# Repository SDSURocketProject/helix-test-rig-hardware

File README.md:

# Helix-Test-Rig-Hardware

Schematics for Helix Project test rig.

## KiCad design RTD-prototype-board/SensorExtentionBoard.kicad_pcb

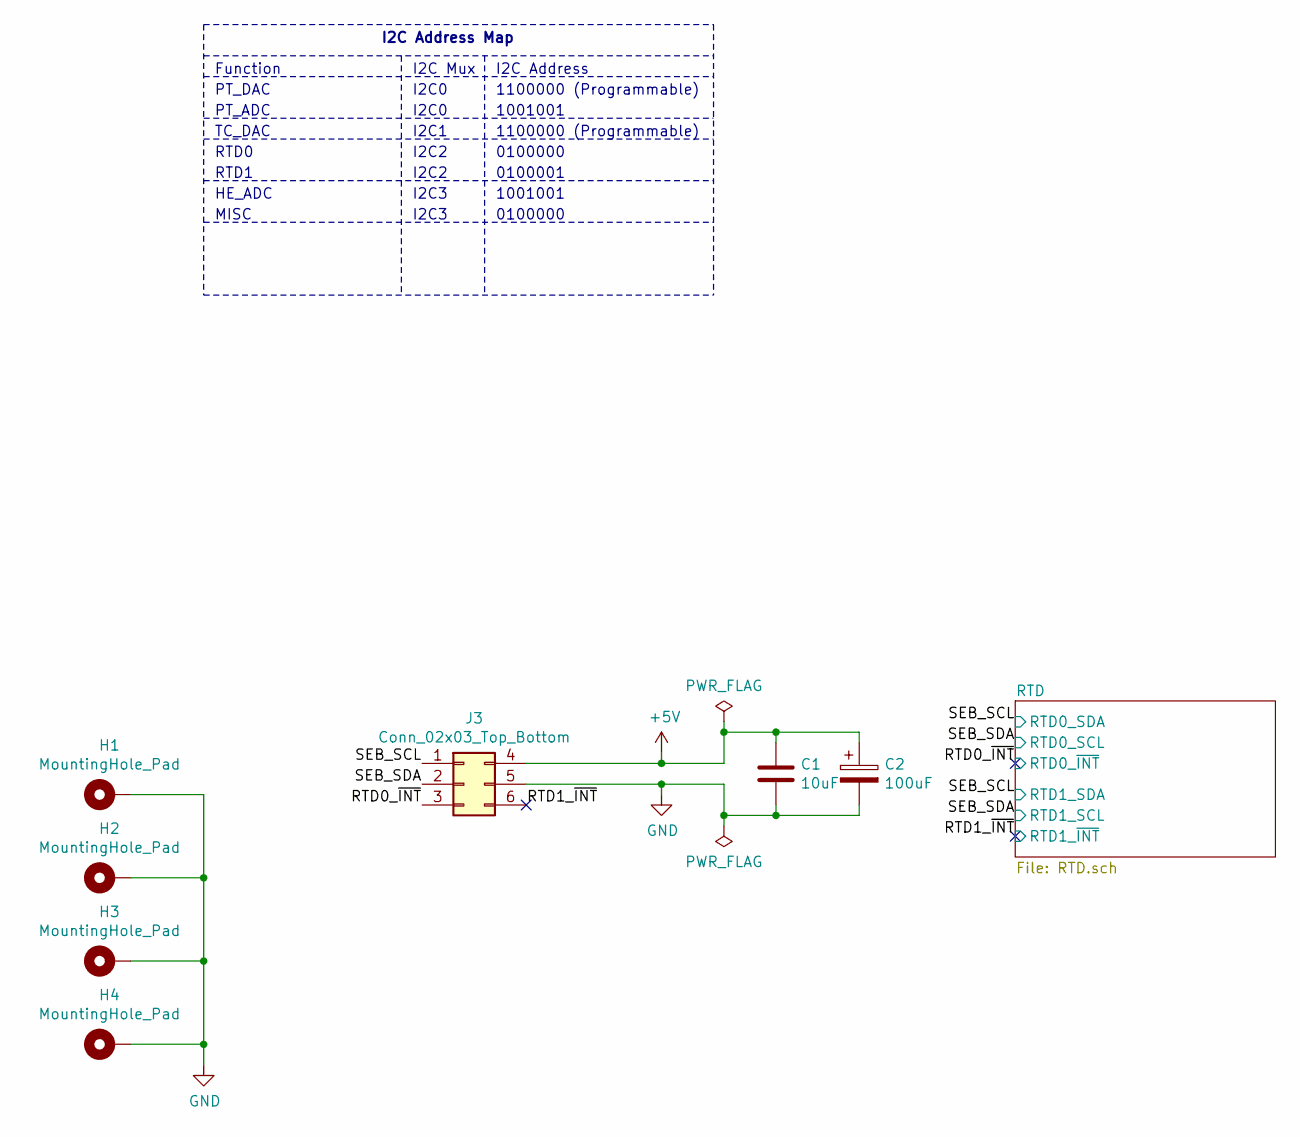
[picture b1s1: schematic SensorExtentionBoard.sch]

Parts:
C1: 10uF; C_1206_3216Metric_Pad1.42x1.75mm_HandSolder
C2: 100uF; CP_Elec_5x5.3
H1, H2, H3, H4: MountingHole_Pad; MountingHole_2.2mm_M2_Pad_Via
J3: Conn_02x03_Top_Bottom; Molex_Micro-Fit_3.0_43045-0612_2x03_P3.00mm_Vertical

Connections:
+5V: C1.1, C2.1, J3.4; also elsewhere on the board
/RTD0_~INT: J3.3; also elsewhere on the board
/RTD1_~INT: J3.6; also elsewhere on the board
/SEB_SCL: J3.1; also elsewhere on the board
/SEB_SDA: J3.2; also elsewhere on the board
GND: C1.2, C2.2, H1.1, H2.1, H3.1, H4.1, J3.5; also elsewhere on the board

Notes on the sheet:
Function
I2C Mux
I2C Address
I2C Address Map
1100000 (Programmable)
PT_DAC
I2C0
PT_ADC
1001001
I2C1
TC_DAC
RTD0
RTD1
0100000
0100001
I2C2
HE_ADC
I2C3
MISC

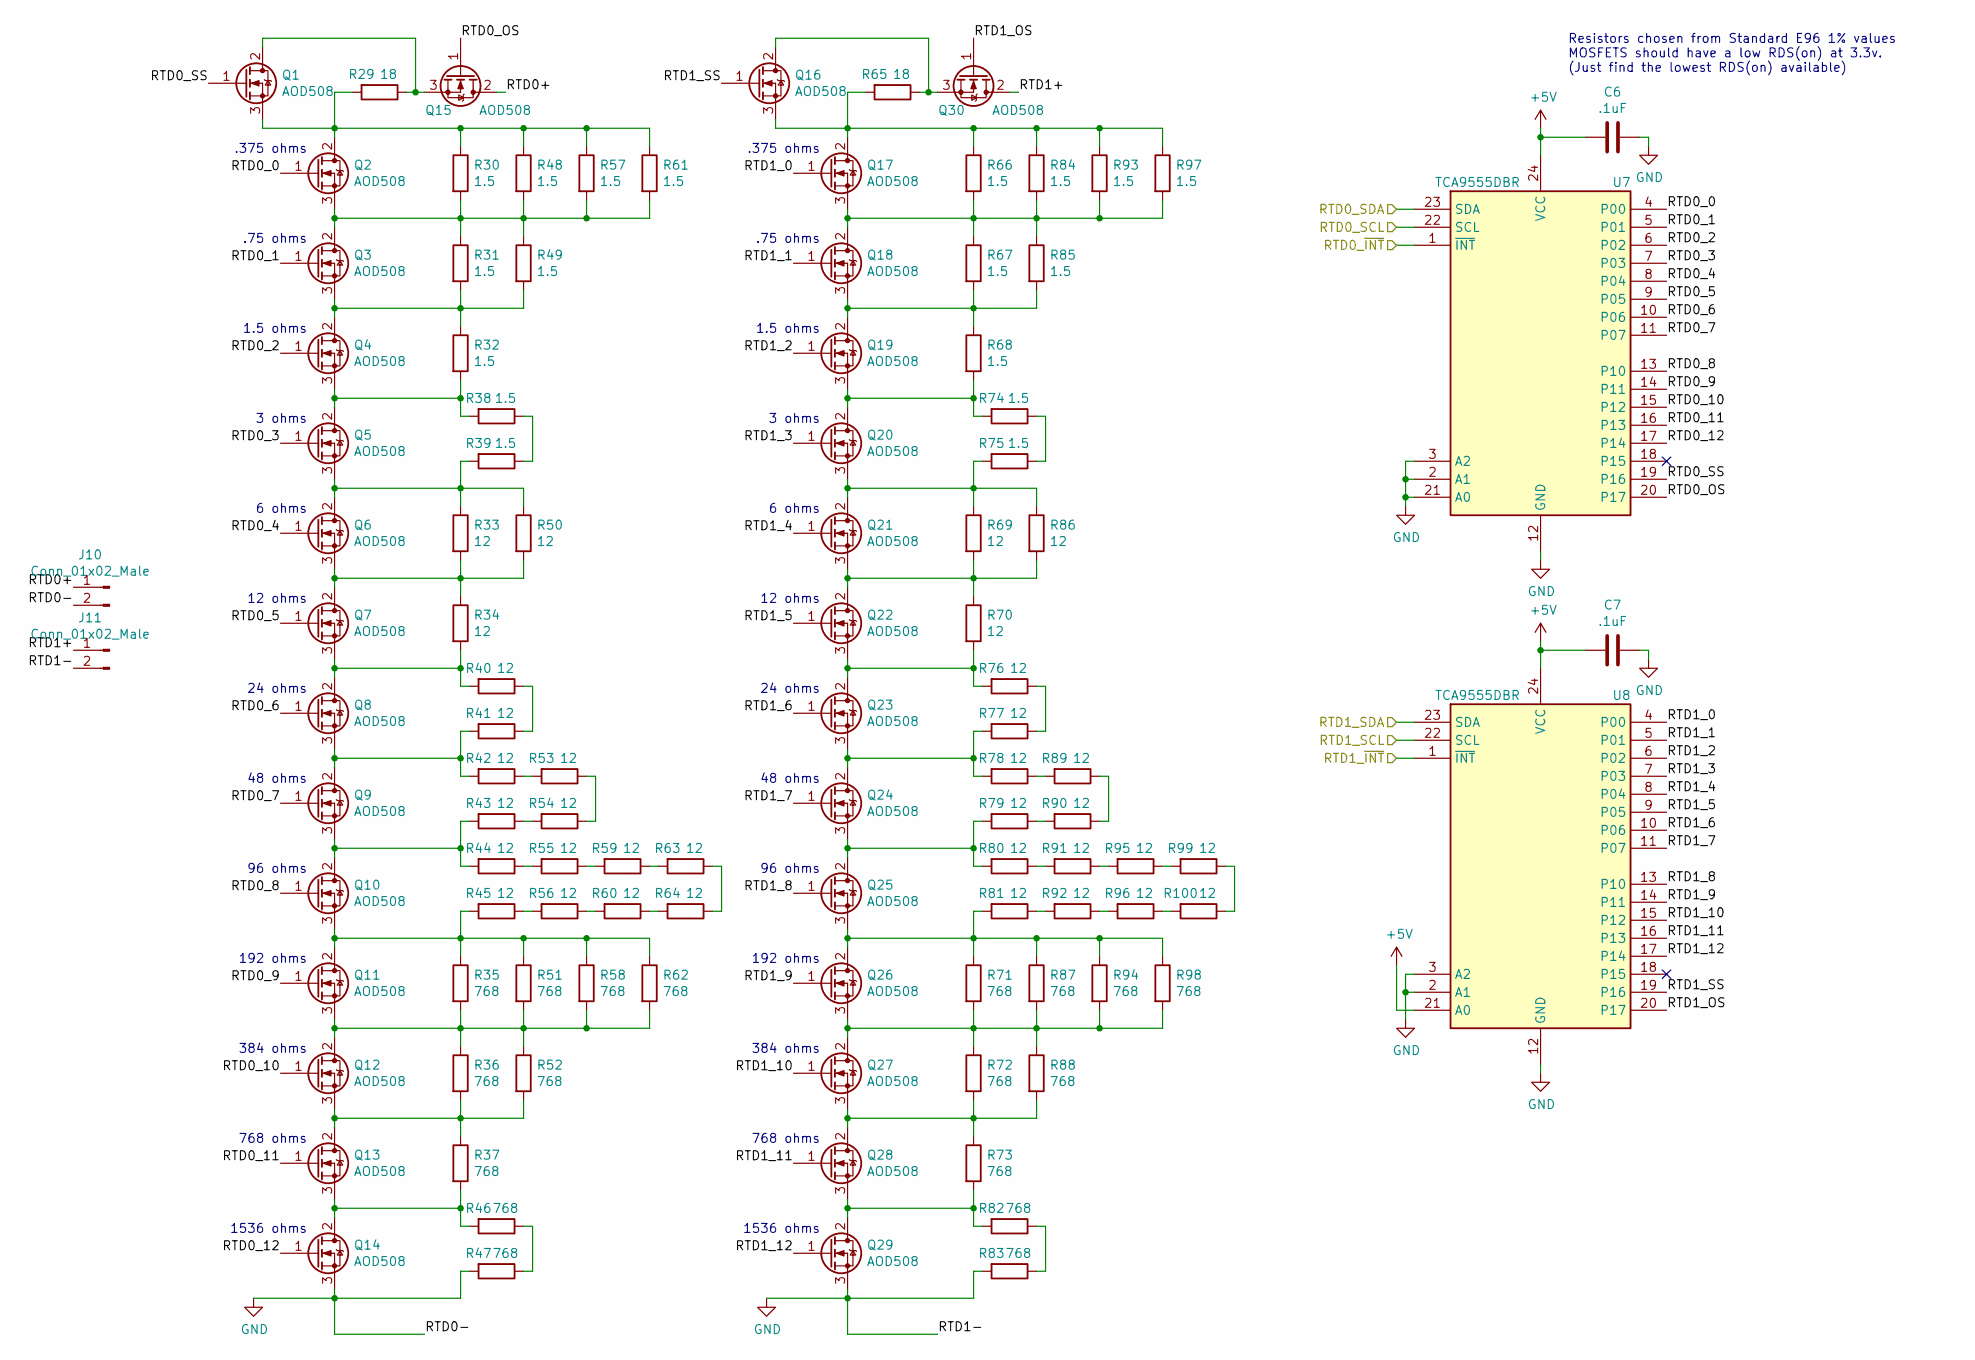
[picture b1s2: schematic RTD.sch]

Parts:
C6, C7: .1uF; C_1206_3216Metric_Pad1.42x1.75mm_HandSolder
J10, J11: Conn_01x02_Male; Molex_MicroClasp_55932-0210_1x02_P2.00mm_Vertical
Q1, Q2, Q3, Q4, Q5, Q6, Q7, Q8, Q9, Q10, Q11, Q12, Q13, Q14, Q15, Q16, Q17, Q18, Q19, Q20, Q21, Q22, Q23, Q24, Q25, Q26, Q27, Q28, Q29, Q30: AOD508; TO-252-3_TabPin2
R29, R65: 18; R_1206_3216Metric_Pad1.42x1.75mm_HandSolder
R30, R31, R32, R38, R39, R48, R49, R57, R61, R66, R67, R68, R74, R75, R84, R85, R93, R97: 1.5; R_1206_3216Metric_Pad1.42x1.75mm_HandSolder
R33, R34, R40, R41, R42, R43, R44, R45, R50, R53, R54, R55, R56, R59, R60, R63, R64, R69, R70, R76, R77, R78, R79, R80, R81, R86, R89, R90, R91, R92, R95, R96, R99, R100: 12; R_1206_3216Metric_Pad1.42x1.75mm_HandSolder
R35, R36, R37, R46, R47, R51, R52, R58, R62, R71, R72, R73, R82, R83, R87, R88, R94, R98: 768; R_1206_3216Metric_Pad1.42x1.75mm_HandSolder
U7, U8: TCA9555DBR; SSOP-24_5.3x8.2mm_P0.65mm

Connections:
+5V: C6.2, C7.2, U7.24 (VCC), U8.21 (A0), U8.24 (VCC); also elsewhere on the board
/RTD0_~INT: U7.1 (~INT); also elsewhere on the board
/RTD1_~INT: U8.1 (~INT); also elsewhere on the board
/RTD/RTD0+: J10.1, Q15.2 (D)
/RTD/RTD0_0: Q2.1 (G), U7.4 (P00)
/RTD/RTD0_1: Q3.1 (G), U7.5 (P01)
/RTD/RTD0_2: Q4.1 (G), U7.6 (P02)
/RTD/RTD0_3: Q5.1 (G), U7.7 (P03)
/RTD/RTD0_4: Q6.1 (G), U7.8 (P04)
/RTD/RTD0_5: Q7.1 (G), U7.9 (P05)
/RTD/RTD0_6: Q8.1 (G), U7.10 (P06)
/RTD/RTD0_7: Q9.1 (G), U7.11 (P07)
/RTD/RTD0_8: Q10.1 (G), U7.13 (P10)
/RTD/RTD0_9: Q11.1 (G), U7.14 (P11)
/RTD/RTD0_10: Q12.1 (G), U7.15 (P12)
/RTD/RTD0_11: Q13.1 (G), U7.16 (P13)
/RTD/RTD0_12: Q14.1 (G), U7.17 (P14)
/RTD/RTD0_OS: Q15.1 (G), U7.20 (P17)
/RTD/RTD0_SS: Q1.1 (G), U7.19 (P16)
/RTD/RTD1+: J11.1, Q30.2 (D)
/RTD/RTD1_0: Q17.1 (G), U8.4 (P00)
/RTD/RTD1_1: Q18.1 (G), U8.5 (P01)
/RTD/RTD1_2: Q19.1 (G), U8.6 (P02)
/RTD/RTD1_3: Q20.1 (G), U8.7 (P03)
/RTD/RTD1_4: Q21.1 (G), U8.8 (P04)
/RTD/RTD1_5: Q22.1 (G), U8.9 (P05)
/RTD/RTD1_6: Q23.1 (G), U8.10 (P06)
/RTD/RTD1_7: Q24.1 (G), U8.11 (P07)
/RTD/RTD1_8: Q25.1 (G), U8.13 (P10)
/RTD/RTD1_9: Q26.1 (G), U8.14 (P11)
/RTD/RTD1_10: Q27.1 (G), U8.15 (P12)
/RTD/RTD1_11: Q28.1 (G), U8.16 (P13)
/RTD/RTD1_12: Q29.1 (G), U8.17 (P14)
/RTD/RTD1_OS: Q30.1 (G), U8.20 (P17)
/RTD/RTD1_SS: Q16.1 (G), U8.19 (P16)
/SEB_SCL: U7.23 (SDA), U8.23 (SDA); also elsewhere on the board
/SEB_SDA: U7.22 (SCL), U8.22 (SCL); also elsewhere on the board
GND: C6.1, C7.1, J10.2, J11.2, Q14.3 (S), Q29.3 (S), R47.2, R83.2, U7.2 (A1), U7.3 (A2), U7.12 (GND), U7.21 (A0), U8.2 (A1), U8.3 (A2), U8.12 (GND); also elsewhere on the board
unnamed: Q1.2 (D), Q15.3 (S), R29.1
unnamed: Q1.3 (S), Q2.2 (D), R29.2, R30.1, R48.1, R57.1, R61.1
unnamed: Q2.3 (S), Q3.2 (D), R30.2, R31.1, R48.2, R49.1, R57.2, R61.2
unnamed: Q3.3 (S), Q4.2 (D), R31.2, R32.1, R49.2
unnamed: Q4.3 (S), Q5.2 (D), R32.2, R38.2
unnamed: Q5.3 (S), Q6.2 (D), R33.1, R39.2, R50.1
unnamed: Q6.3 (S), Q7.2 (D), R33.2, R34.1, R50.2
unnamed: Q7.3 (S), Q8.2 (D), R34.2, R40.2
unnamed: Q8.3 (S), Q9.2 (D), R41.2, R42.2
unnamed: Q9.3 (S), Q10.2 (D), R43.2, R44.2
unnamed: Q10.3 (S), Q11.2 (D), R35.1, R45.2, R51.1, R58.1, R62.1
unnamed: Q11.3 (S), Q12.2 (D), R35.2, R36.1, R51.2, R52.1, R58.2, R62.2
unnamed: Q12.3 (S), Q13.2 (D), R36.2, R37.1, R52.2
unnamed: Q13.3 (S), Q14.2 (D), R37.2, R46.2
unnamed: Q16.2 (D), Q30.3 (S), R65.1
unnamed: Q16.3 (S), Q17.2 (D), R65.2, R66.1, R84.1, R93.1, R97.1
unnamed: Q17.3 (S), Q18.2 (D), R66.2, R67.1, R84.2, R85.1, R93.2, R97.2
unnamed: Q18.3 (S), Q19.2 (D), R67.2, R68.1, R85.2
unnamed: Q19.3 (S), Q20.2 (D), R68.2, R74.2
unnamed: Q20.3 (S), Q21.2 (D), R69.1, R75.2, R86.1
unnamed: Q21.3 (S), Q22.2 (D), R69.2, R70.1, R86.2
unnamed: Q22.3 (S), Q23.2 (D), R70.2, R76.2
unnamed: Q23.3 (S), Q24.2 (D), R77.2, R78.2
unnamed: Q24.3 (S), Q25.2 (D), R79.2, R80.2
unnamed: Q25.3 (S), Q26.2 (D), R71.1, R81.2, R87.1, R94.1, R98.1
unnamed: Q26.3 (S), Q27.2 (D), R71.2, R72.1, R87.2, R88.1, R94.2, R98.2
unnamed: Q27.3 (S), Q28.2 (D), R72.2, R73.1, R88.2
unnamed: Q28.3 (S), Q29.2 (D), R73.2, R82.2
unnamed: R38.1, R39.1
unnamed: R40.1, R41.1
unnamed: R42.1, R53.2
unnamed: R43.1, R54.2
unnamed: R44.1, R55.2
unnamed: R45.1, R56.2
unnamed: R46.1, R47.1
unnamed: R53.1, R54.1
unnamed: R55.1, R59.2
unnamed: R56.1, R60.2
unnamed: R59.1, R63.2
unnamed: R60.1, R64.2
unnamed: R63.1, R64.1
unnamed: R74.1, R75.1
unnamed: R76.1, R77.1
unnamed: R78.1, R89.2
unnamed: R79.1, R90.2
unnamed: R80.1, R91.2
unnamed: R81.1, R92.2
unnamed: R82.1, R83.1
unnamed: R89.1, R90.1
unnamed: R91.1, R95.2
unnamed: R92.1, R96.2
unnamed: R95.1, R99.2
unnamed: R99.1, R100.1
unnamed: R96.1, R100.2

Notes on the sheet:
Resistors chosen from Standard E96 1% values MOSFETS should have a low RDS(on) at 3.3v. (Just find the lowest RDS(on) available)
1536 ohms
768 ohms
384 ohms
192 ohms
96 ohms
48 ohms
24 ohms
12 ohms
6 ohms
3 ohms
1.5 ohms
.75 ohms
.375 ohms

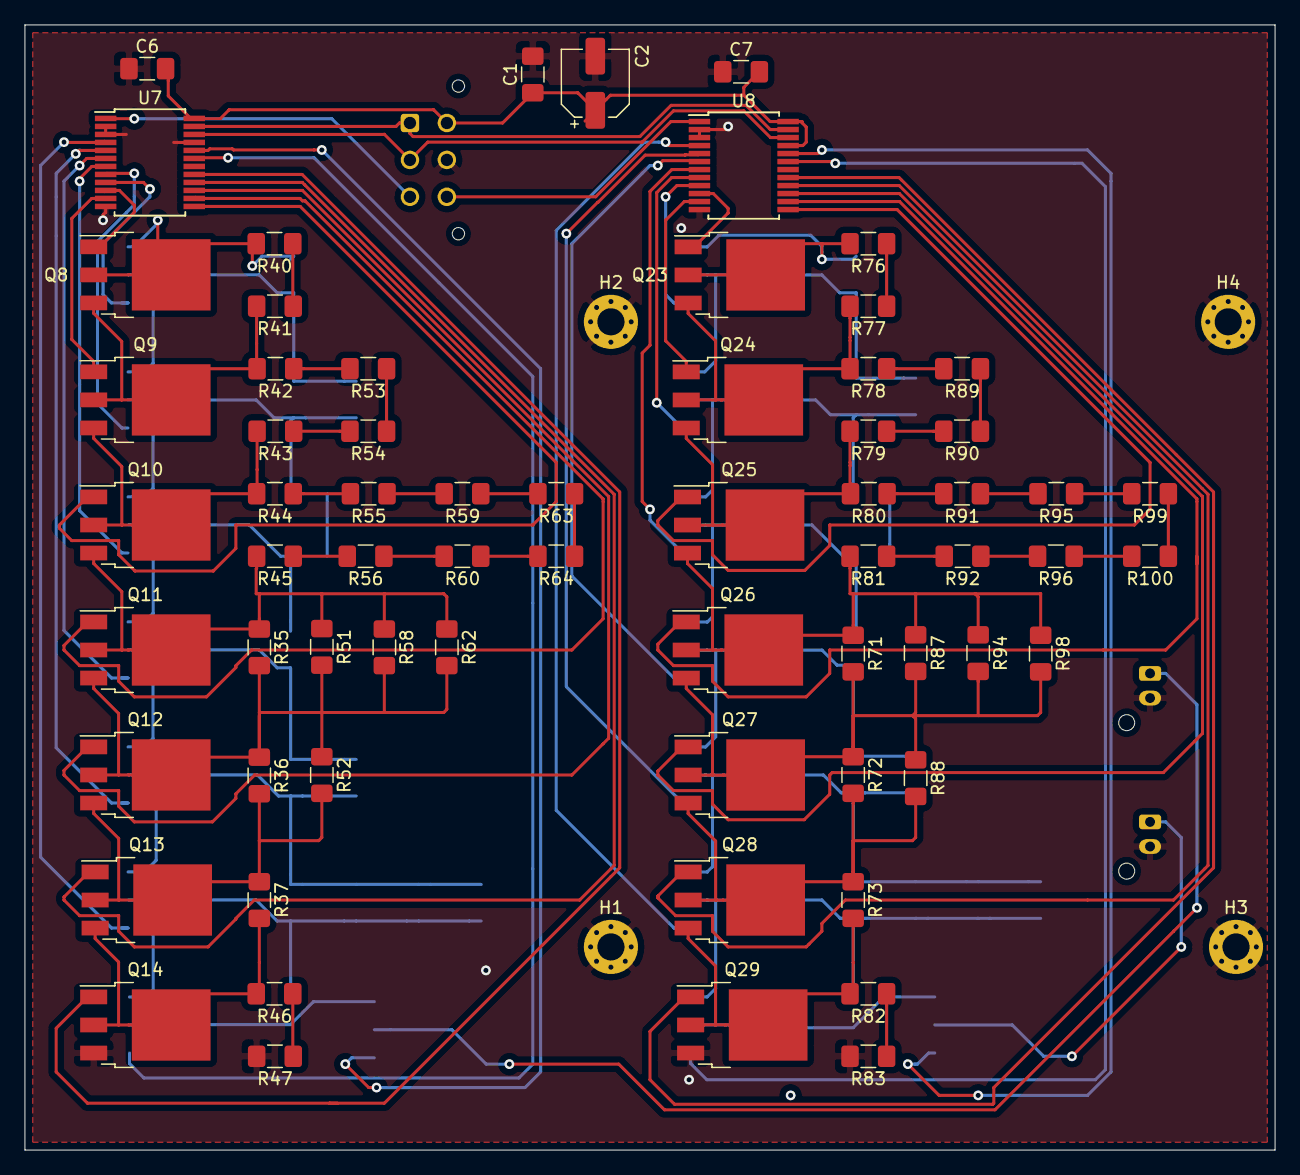
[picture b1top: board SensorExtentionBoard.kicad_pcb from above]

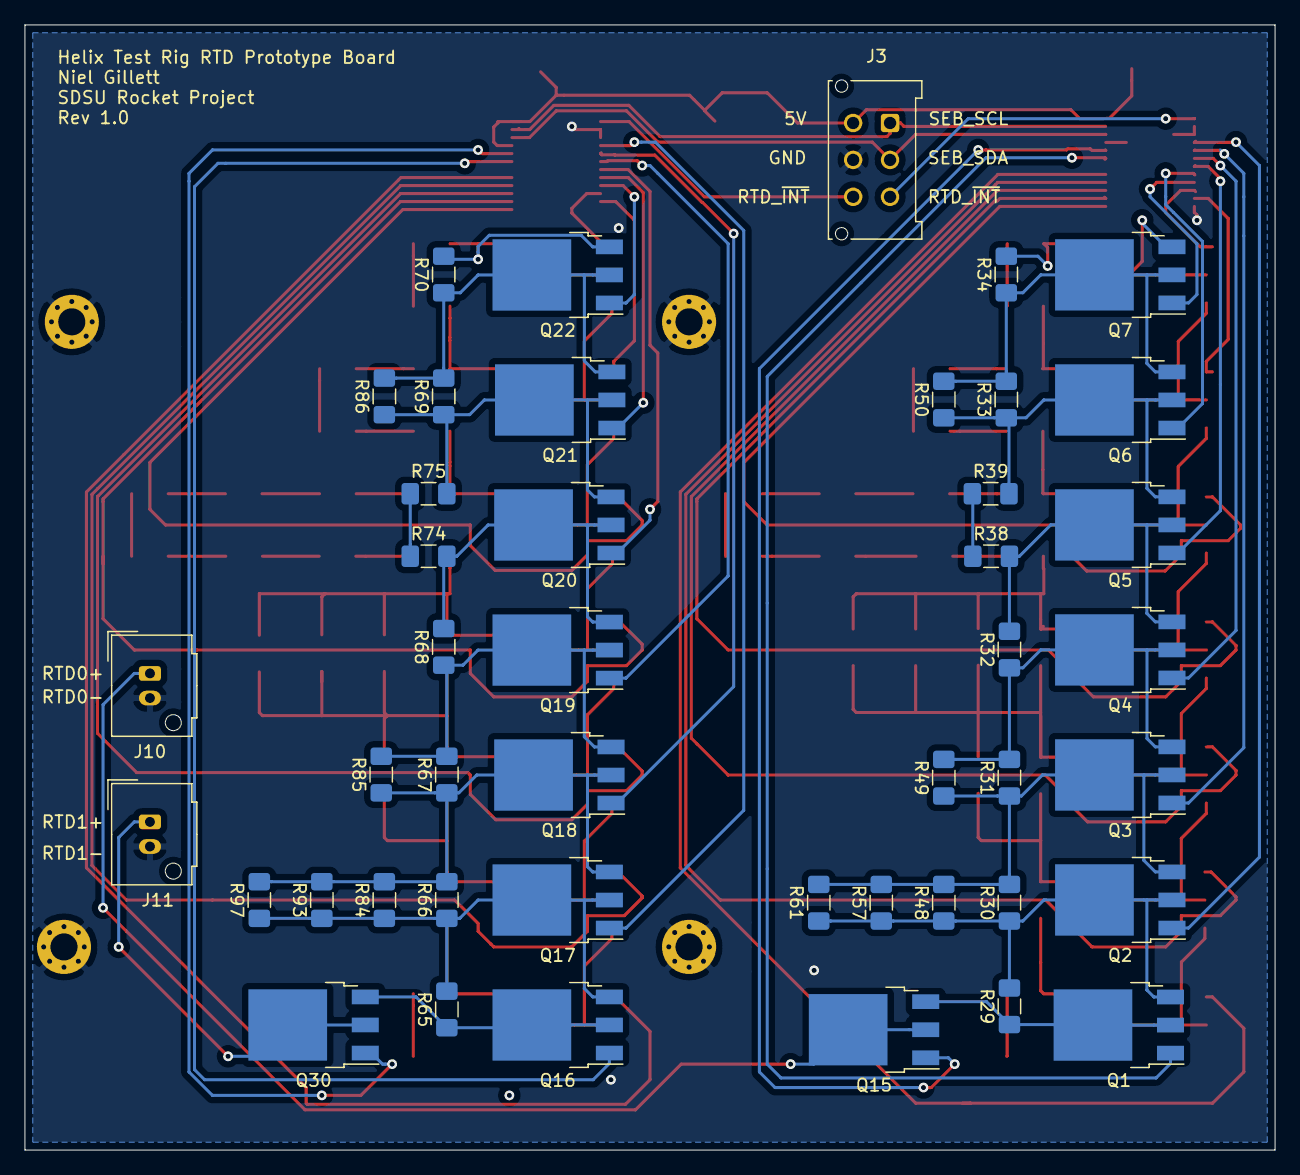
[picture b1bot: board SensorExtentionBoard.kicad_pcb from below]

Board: 2 copper layers, 101.6 x 91.4 mm, 115 parts (45 on the bottom side), 92 nets.

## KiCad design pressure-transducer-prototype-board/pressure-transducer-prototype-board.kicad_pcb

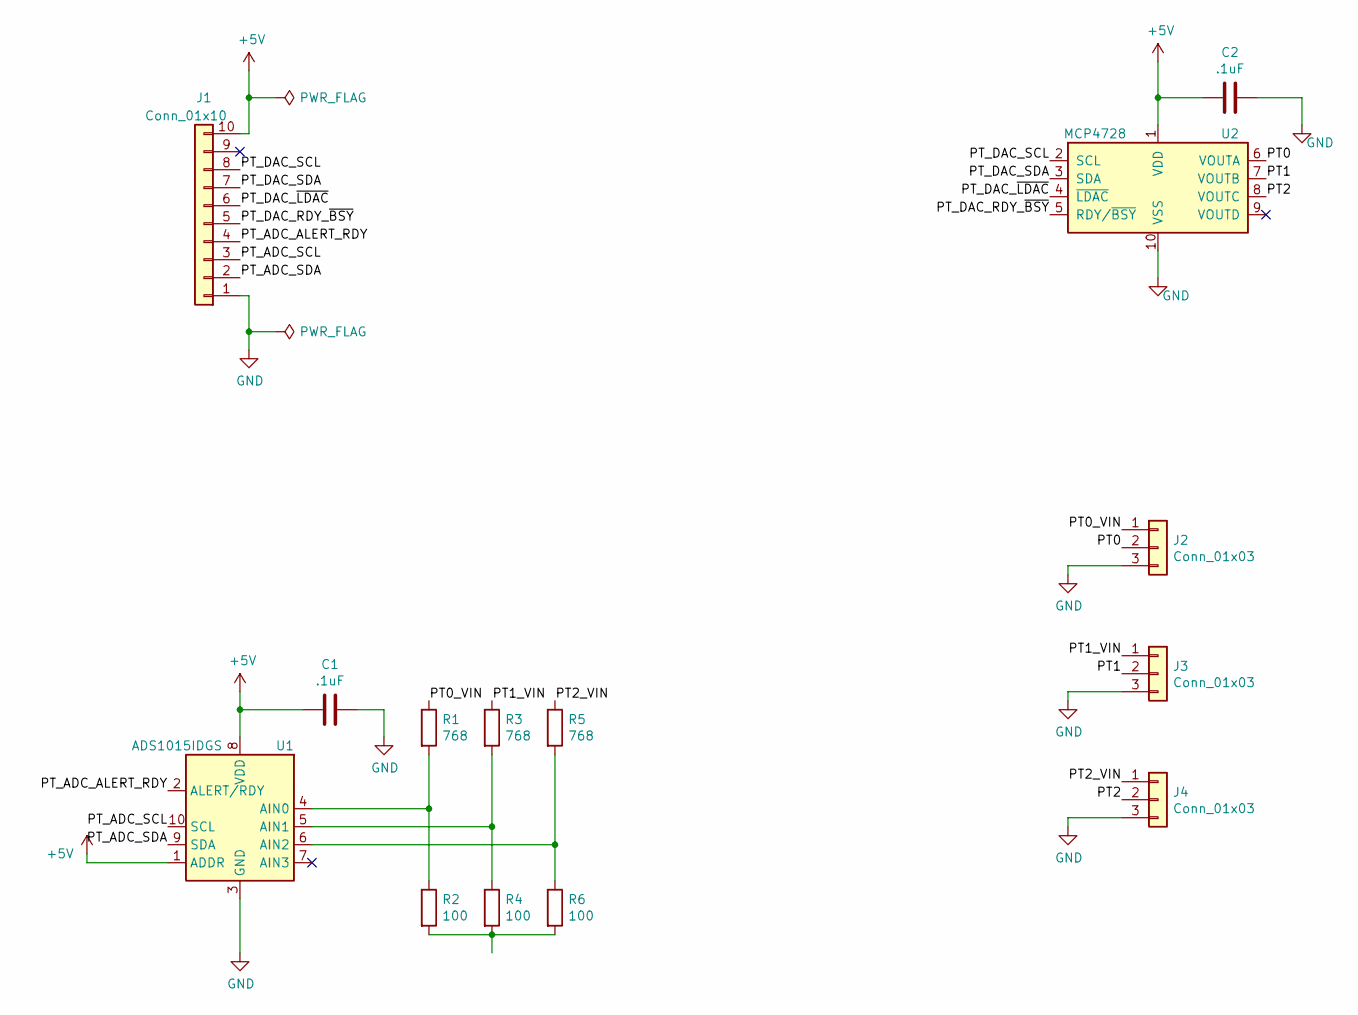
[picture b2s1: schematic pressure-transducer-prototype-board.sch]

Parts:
C1, C2: .1uF; C_1206_3216Metric_Pad1.42x1.75mm_HandSolder
J1: Conn_01x10; PinHeader_1x10_P2.54mm_Vertical
J2, J3, J4: Conn_01x03; PinHeader_1x03_P2.54mm_Vertical
R1, R3, R5: 768; R_1206_3216Metric_Pad1.42x1.75mm_HandSolder
R2, R4, R6: 100; R_1206_3216Metric_Pad1.42x1.75mm_HandSolder
U1: ADS1015IDGS; VSSOP-10_3x3mm_P0.5mm
U2: MCP4728; MSOP-10_3x3mm_P0.5mm

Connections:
+5V: C1.2, C2.2, J1.10, U1.1 (ADDR), U1.8 (VDD), U2.1 (VDD)
/PT0: J2.2, U2.6 (VOUTA)
/PT0_VIN: J2.1, R1.1
/PT1: J3.2, U2.7 (VOUTB)
/PT1_VIN: J3.1, R3.1
/PT2: J4.2, U2.8 (VOUTC)
/PT2_VIN: J4.1, R5.1
/PT_ADC_ALERT_RDY: J1.4, U1.2 (ALERT/RDY)
/PT_ADC_SCL: J1.3, U1.10 (SCL)
/PT_ADC_SDA: J1.2, U1.9 (SDA)
/PT_DAC_RDY_~BSY~: J1.5, U2.5 (RDY/~BSY)
/PT_DAC_SCL: J1.8, U2.2 (SCL)
/PT_DAC_SDA: J1.7, U2.3 (SDA)
/PT_DAC_~LDAC~: J1.6, U2.4 (~LDAC)
GND: C1.1, C2.1, J1.1, J2.3, J3.3, J4.3, U1.3 (GND), U2.10 (VSS)
unnamed: R1.2, R2.1, U1.4 (AIN0)
unnamed: R2.2, R4.2, R6.2
unnamed: R3.2, R4.1, U1.5 (AIN1)
unnamed: R5.2, R6.1, U1.6 (AIN2)

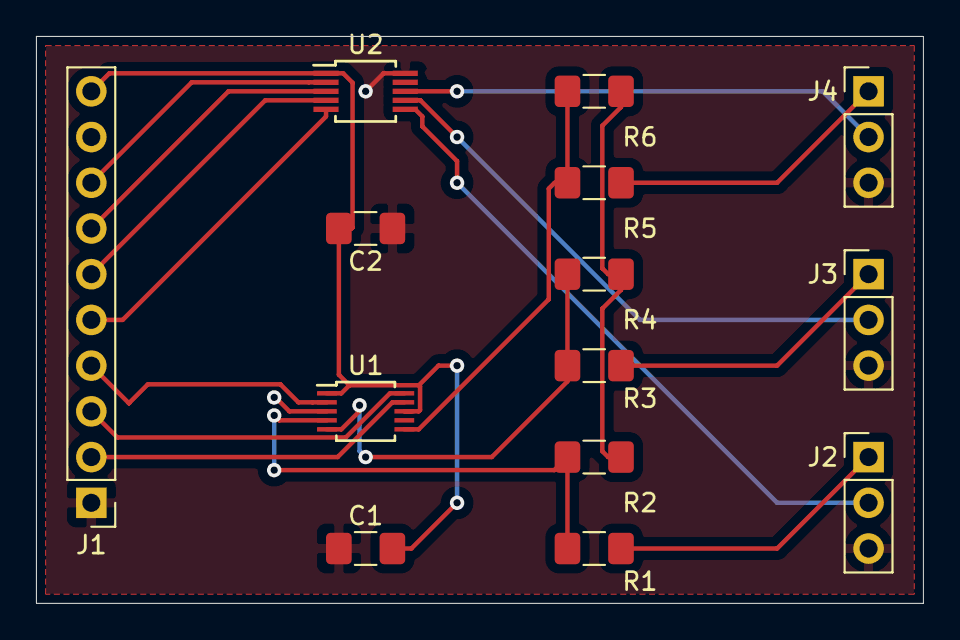
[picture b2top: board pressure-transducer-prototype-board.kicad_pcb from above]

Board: 2 copper layers, 49.3 x 31.5 mm, 14 parts (0 on the bottom side), 19 nets.

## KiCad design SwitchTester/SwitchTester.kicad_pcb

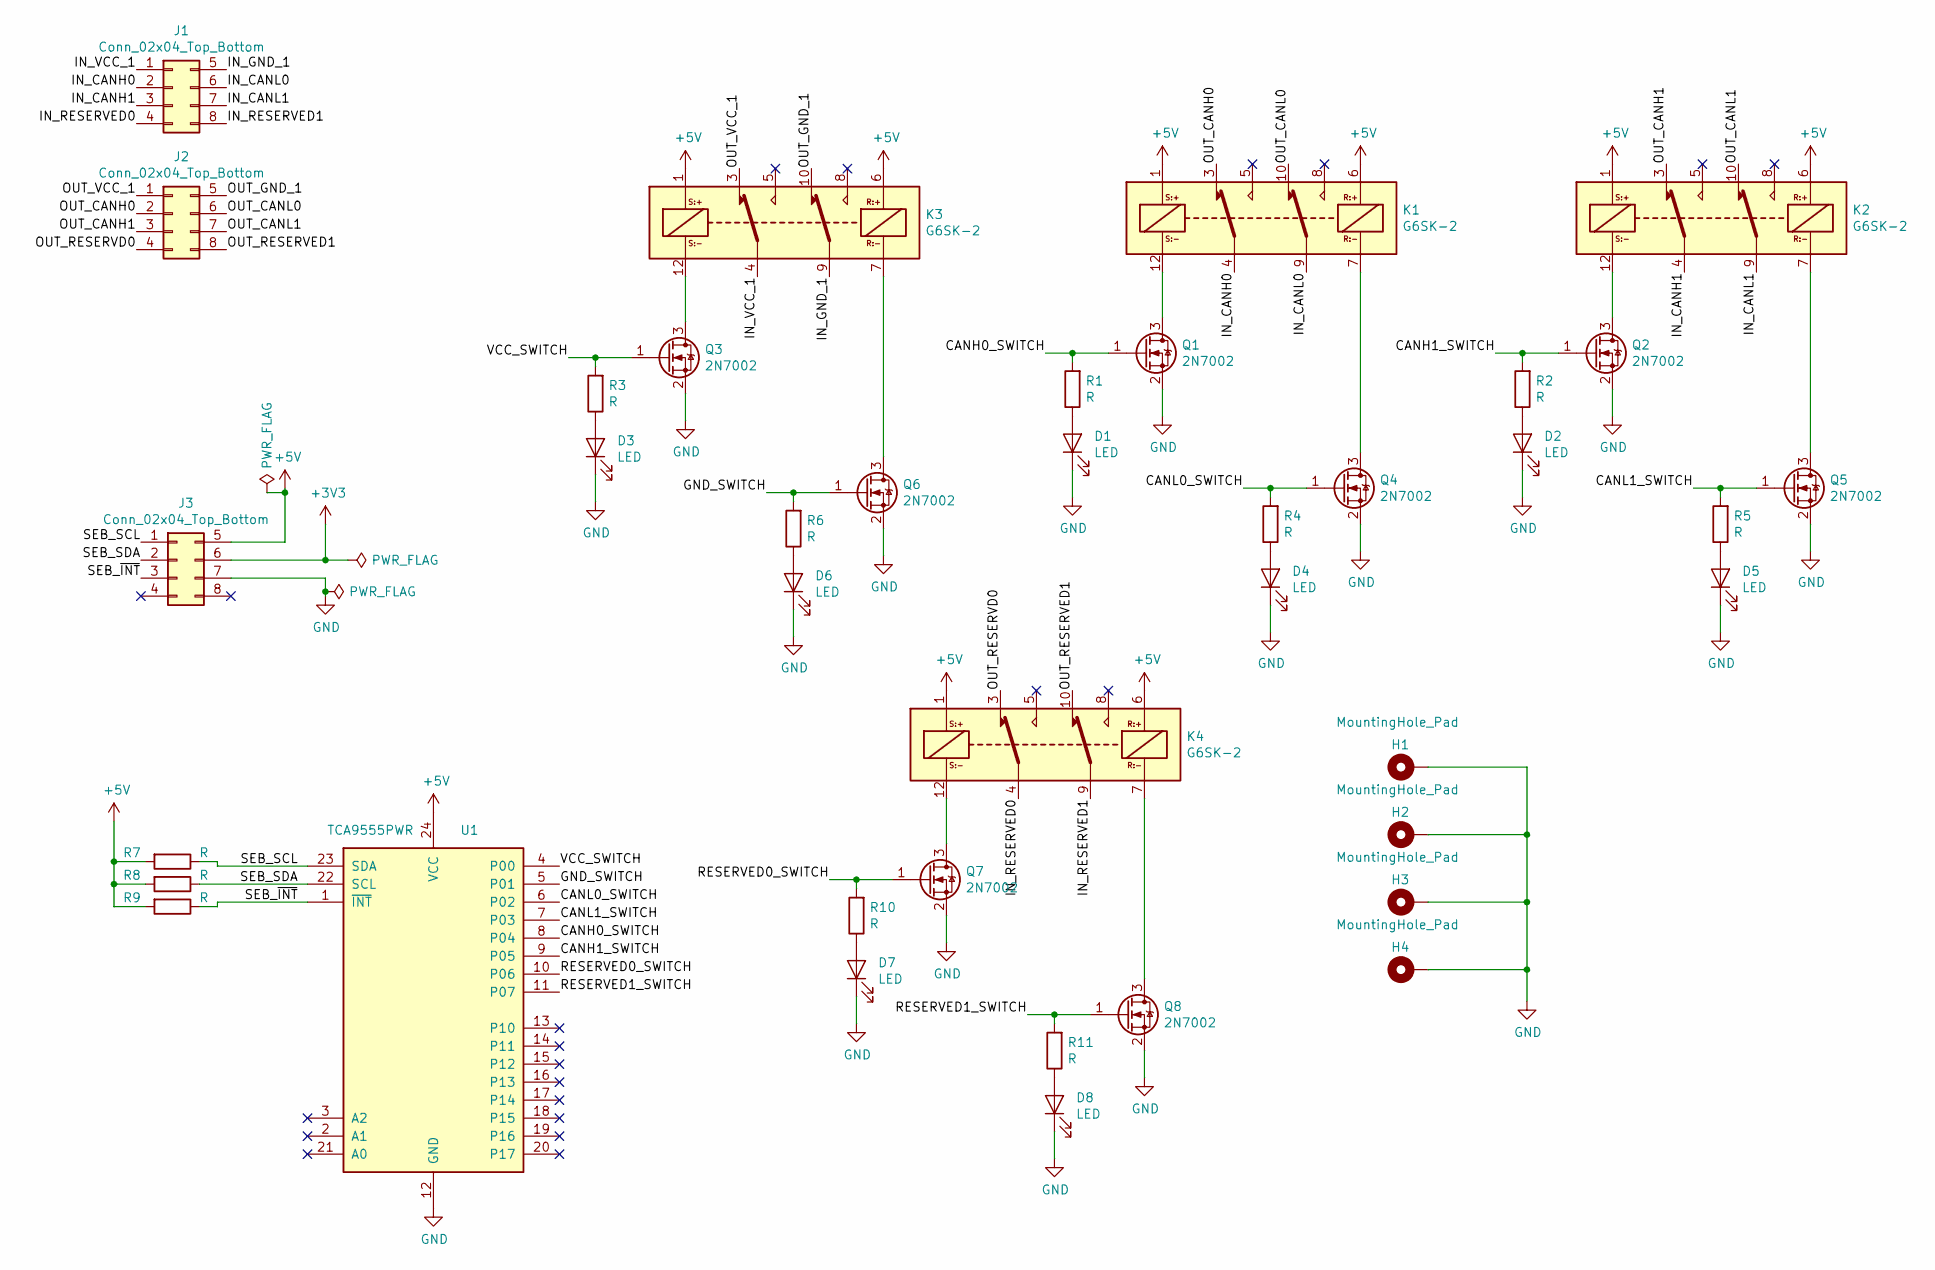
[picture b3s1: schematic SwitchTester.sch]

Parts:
D1, D2, D3, D4, D5, D6, D7, D8: LED; D_2010_5025Metric
H1, H2, H3, H4: MountingHole_Pad; MountingHole_2.2mm_M2_Pad_Via
J1, J2, J3: Conn_02x04_Top_Bottom; Molex_Micro-Fit_3.0_43045-0812_2x04_P3.00mm_Vertical
K1, K2, K3, K4: G6SK-2; RELAY_EC2-5TNU
Q1, Q2, Q3, Q4, Q5, Q6, Q7, Q8: 2N7002; SOT-23
R1, R2, R3, R4, R5, R6, R7, R8, R9, R10, R11: R; R_1206_3216Metric_Pad1.42x1.75mm_HandSolder
U1: TCA9555PWR; TSSOP-24_4.4x7.8mm_P0.65mm

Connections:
+3V3: J3.6
+5V: J3.5, K1.1, K1.6, K2.1, K2.6, K3.1, K3.6, K4.1, K4.6, R7.2, R8.2, R9.2, U1.24 (VCC)
/CANH0_SWITCH: Q1.1 (G), R1.2, U1.8 (P04)
/CANH1_SWITCH: Q2.1 (G), R2.2, U1.9 (P05)
/CANL0_SWITCH: Q4.1 (G), R4.2, U1.6 (P02)
/CANL1_SWITCH: Q5.1 (G), R5.2, U1.7 (P03)
/GND_SWITCH: Q6.1 (G), R6.2, U1.5 (P01)
/IN_CANH0: J1.2, K1.4
/IN_CANH1: J1.3, K2.4
/IN_CANL0: J1.6, K1.9
/IN_CANL1: J1.7, K2.9
/IN_GND_1: J1.5, K3.9
/IN_RESERVED0: J1.4, K4.4
/IN_RESERVED1: J1.8, K4.9
/IN_VCC_1: J1.1, K3.4
/OUT_CANH0: J2.2, K1.3
/OUT_CANH1: J2.3, K2.3
/OUT_CANL0: J2.6, K1.10
/OUT_CANL1: J2.7, K2.10
/OUT_GND_1: J2.5, K3.10
/OUT_RESERVD0: J2.4, K4.3
/OUT_RESERVED1: J2.8, K4.10
/OUT_VCC_1: J2.1, K3.3
/RESERVED0_SWITCH: Q7.1 (G), R10.2, U1.10 (P06)
/RESERVED1_SWITCH: Q8.1 (G), R11.2, U1.11 (P07)
/SEB_SCL: J3.1, R7.1, U1.23 (SDA)
/SEB_SDA: J3.2, R8.1, U1.22 (SCL)
/SEB_~INT: J3.3, R9.1, U1.1 (~INT)
/VCC_SWITCH: Q3.1 (G), R3.2, U1.4 (P00)
GND: D1.1 (K), D2.1 (K), D3.1 (K), D4.1 (K), D5.1 (K), D6.1 (K), D7.1 (K), D8.1 (K), H1.1, H2.1, H3.1, H4.1, J3.7, Q1.2 (S), Q2.2 (S), Q3.2 (S), Q4.2 (S), Q5.2 (S), Q6.2 (S), Q7.2 (S), Q8.2 (S), U1.12 (GND)
unnamed: D1.2 (A), R1.1
unnamed: D2.2 (A), R2.1
unnamed: D3.2 (A), R3.1
unnamed: D4.2 (A), R4.1
unnamed: D5.2 (A), R5.1
unnamed: D6.2 (A), R6.1
unnamed: D7.2 (A), R10.1
unnamed: D8.2 (A), R11.1
unnamed: K1.7, Q4.3 (D)
unnamed: K1.12, Q1.3 (D)
unnamed: K2.7, Q5.3 (D)
unnamed: K2.12, Q2.3 (D)
unnamed: K3.7, Q6.3 (D)
unnamed: K3.12, Q3.3 (D)
unnamed: K4.7, Q8.3 (D)
unnamed: K4.12, Q7.3 (D)

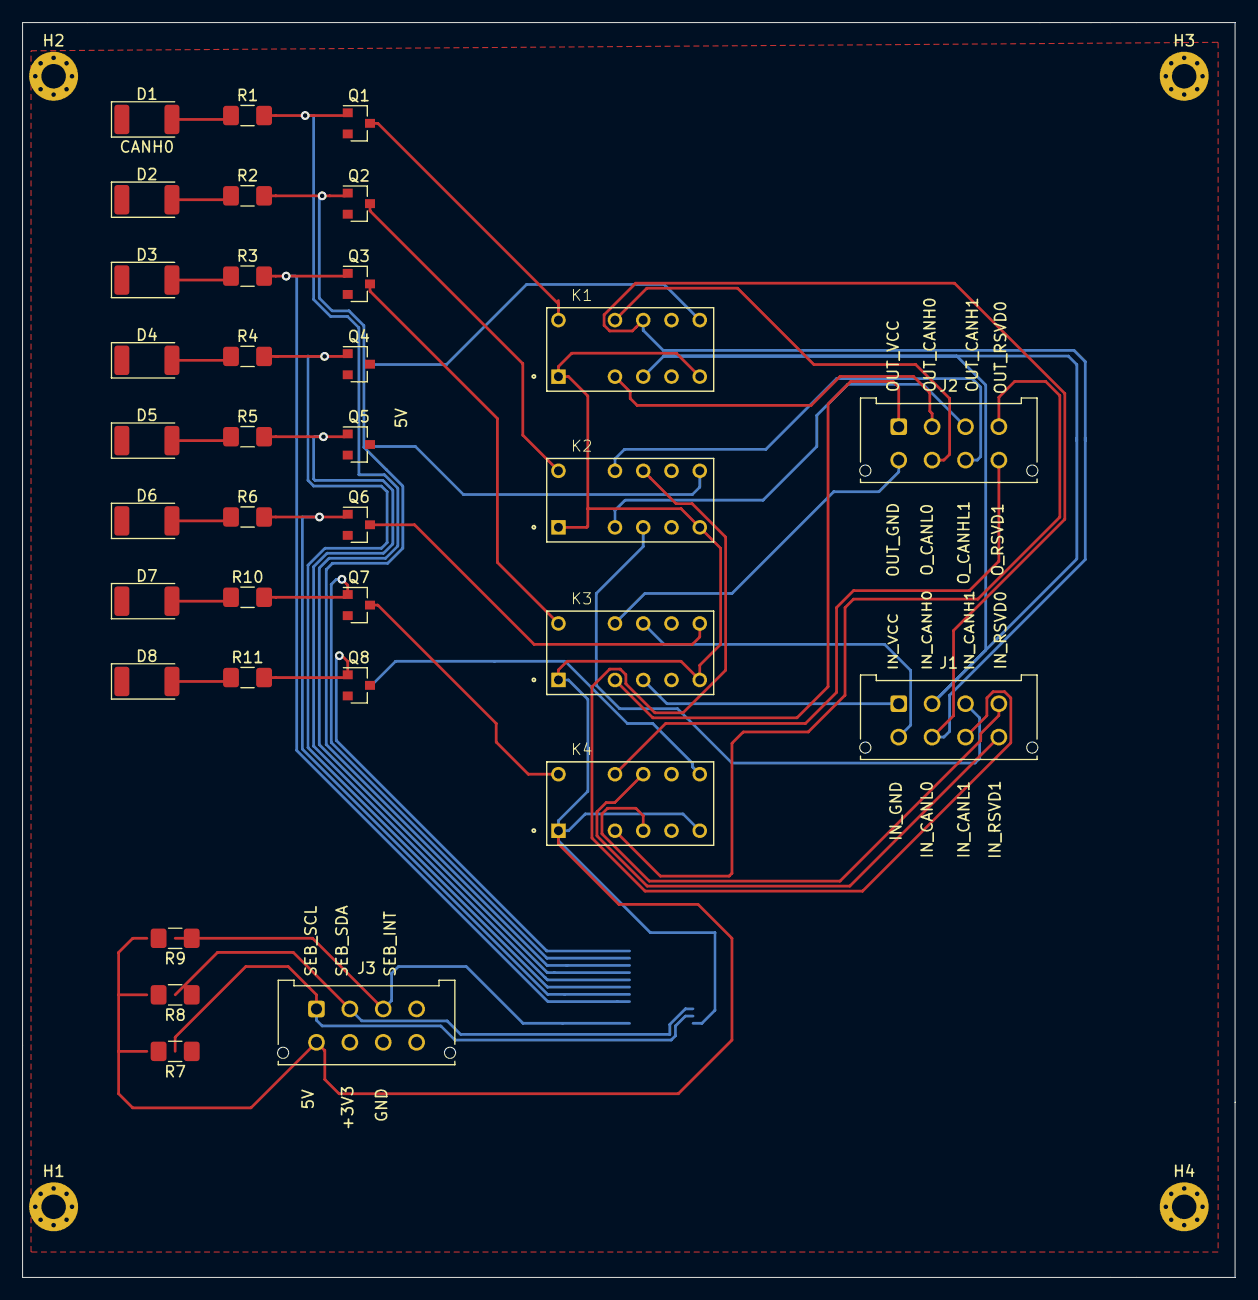
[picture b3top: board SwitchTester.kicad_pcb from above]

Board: 2 copper layers, 109.0 x 112.8 mm, 39 parts (1 on the bottom side), 45 nets.

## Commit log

2019-12-27 Added pressure transducer and RTD test rig circuits
2019-12-27 Added short circuit and open circuit test functionality to RTD test circuit
2019-12-27 Added Hall Effect sensor test circuit
2019-12-27 Added top level page and made various fixes in other pages of SEB test rig board
2019-12-28 Moved some stuff and added footprints to components
2019-12-28 Added decoupling caps
2020-01-03 Add .gitlab-ci.yml with ability to compile and deploy SensorExtentionBoard schematic pdfs
2020-01-03 Test .gitlab-ci.yml
2020-01-03 Forgot to put '-' in front of arguments in .gitlab-ci.yml
2020-01-03 Added new pre-commit hook
    Created a new pre-commit hook that will ensure that there a new pdf of
    the schematic has been created before commiting. It doesn't actually
    check if the new pdf reflects the new schematic, it just ensures that
    a new pdf has been created at some point. The hooks don't immediately
    take effect, you need to run 'git config core.hooksPath hooks' before
    they will take effect.
2020-01-03 Created .gitignore
    Created .gitignore file from github kicad template found at
    https://github.com/github/gitignore/blob/master/KiCad.gitignore.
    Added .plt files to prevent unnecessary plotted output from being
    commited.
2020-01-03 Removed cached files that are now in .gitignore
2020-01-03 Updated .gitlab-ci.yml to push schematic pdf to server
2020-01-03 Updated .gitlab-ci.yml to install git ssh keys
2020-01-10 Added ground reference for RTD test section
2020-01-10 Replaced ADS1115 with ADS1015 on PT page
    The ADS1115 is being used to read the voltages provided by the Helix
    system to the pressure transducers. The ADS1015 is already doing
    the same job for the Hall Effect sensors, however the ADS1015 has
    4 bits lower accuracy. High accuracy is not needed for this
    application so be replacing the ADS1115 with the ADS1015 we can
    reduce cost and more importantly reduce BOM size making the project
2020-01-11 Added header for programming the EEPROM memory on the SEB
    Adding this header may allow the test rig to load new memory configs
    onto the SEB under test prior to running tests. This will allow
    greater ability for automation of testing when the new software
    requires a change to the config onboard the SEB.
2020-01-14 Changed component footprints to conform to RP standard components
2020-04-10 Created switch tester board
2020-06-04 Initial revision of PT prototype board
2020-06-04 Initial commit of RTD-prototype-board
